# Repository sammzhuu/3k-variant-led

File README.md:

# 3k-variant-led
 a rehash of my scrapped 6k build now with 3k and leds 

if you want to build this project yourself, here are some useful guides: 
https://docs.google.com/document/d/1xsjb1sf3pxFw8bXC4gNhWsFhWNOthMoyz6RiJc1UtVI/edit?tab=t.0
https://www.youtube.com/watch?v=Ov2vdJQmaAw
https://www.masterzen.fr/2020/05/03/designing-a-keyboard-part-1/
https://wiki.ai03.com/books/pcb-design/page/pcb-guide-part-1---preparations

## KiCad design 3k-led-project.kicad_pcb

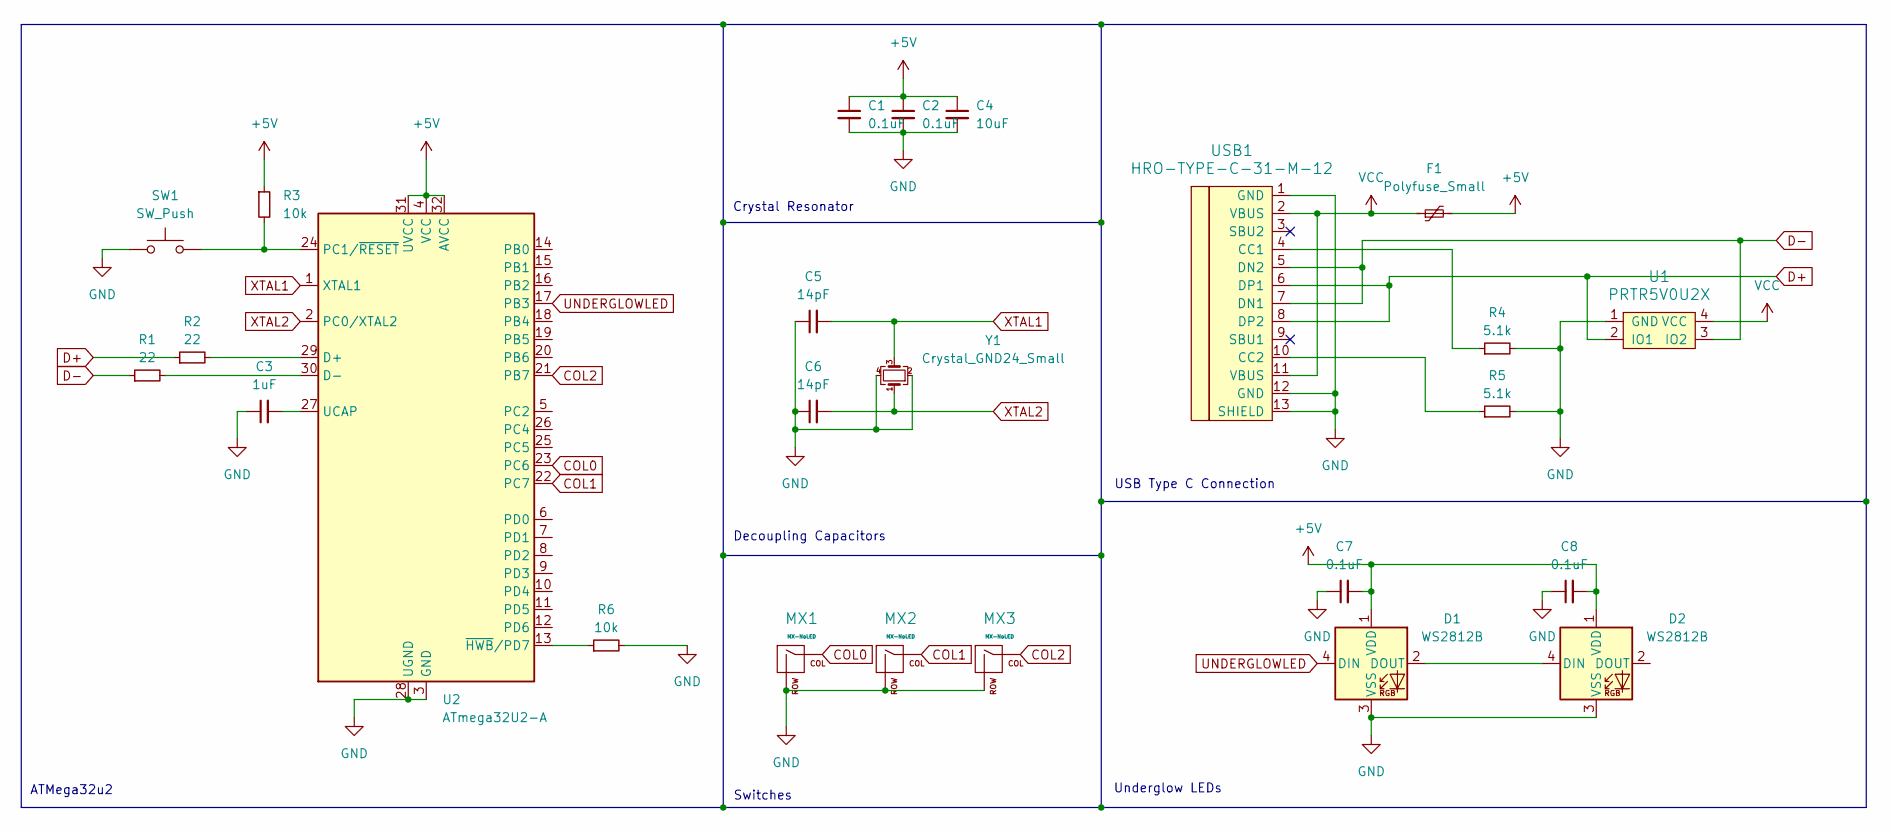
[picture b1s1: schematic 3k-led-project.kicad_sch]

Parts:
C1, C2, C7, C8: 0.1uF; C_0805_2012Metric_Pad1.18x1.45mm_HandSolder
C3: 1uF; C_0805_2012Metric_Pad1.18x1.45mm_HandSolder
C4: 10uF; C_0805_2012Metric_Pad1.18x1.45mm_HandSolder
C5, C6: 14pF; C_0805_2012Metric_Pad1.18x1.45mm_HandSolder
D1, D2: WS2812B; LED_WS2812B_PLCC4_5.0x5.0mm_P3.2mm
F1: Polyfuse_Small; Fuse_1206_3216Metric_Pad1.42x1.75mm_HandSolder
MX1, MX2, MX3: MX-NoLED; MXOnly-1U-Hotswap
R1, R2: 22; R_0805_2012Metric_Pad1.20x1.40mm_HandSolder
R3, R6: 10k; R_0805_2012Metric_Pad1.20x1.40mm_HandSolder
R4, R5: 5.1k; R_0805_2012Metric_Pad1.20x1.40mm_HandSolder
SW1: SW_Push; SKQGADE010
U1: PRTR5V0U2X; SOT143B
U2: ATmega32U2-A; TQFP-32_7x7mm_P0.8mm
USB1: HRO-TYPE-C-31-M-12; HRO-TYPE-C-31-M-12-HandSoldering
Y1: Crystal_GND24_Small; Crystal_SMD_3225-4Pin_3.2x2.5mm_HandSoldering

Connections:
+5V: C1.1, C2.1, C4.1, C7.2, C8.2, D1.1 (VDD), D2.1 (VDD), F1.2, R3.1, U2.4 (VCC), U2.31 (UVCC), U2.32 (AVCC)
COL0: MX1.1 (COL), U2.23 (PC6)
COL1: MX2.1 (COL), U2.22 (PC7)
COL2: MX3.1 (COL), U2.21 (PB7)
D+: R2.1, U1.2 (IO1), USB1.6 (DP1), USB1.8 (DP2)
D-: R1.1, U1.3 (IO2), USB1.5 (DN2), USB1.7 (DN1)
GND: C1.2, C2.2, C3.1, C4.2, C5.1, C6.1, C7.1, C8.1, D1.3 (VSS), D2.3 (VSS), MX1.2 (ROW), MX2.2 (ROW), MX3.2 (ROW), R4.2, R5.2, R6.2, SW1.1, U1.1 (GND), U2.3 (GND), U2.28 (UGND), USB1.1 (GND), USB1.12 (GND), USB1.13 (SHIELD), Y1.2, Y1.4
unnamed: D1.2 (DOUT), D2.4 (DIN)
unnamed: R2.2, U2.29 (D+)
unnamed: R1.2, U2.30 (D-)
unnamed: R3.2, SW1.2, U2.24 (PC1/~RESET)
unnamed: C3.2, U2.27 (UCAP)
unnamed: R6.1, U2.13 (~HWB/PD7)
unnamed: R4.1, USB1.4 (CC1)
unnamed: R5.1, USB1.10 (CC2)
UNDERGLOWLED: D1.4 (DIN), U2.17 (PB3)
VCC: F1.1, U1.4 (VCC), USB1.2 (VBUS), USB1.11 (VBUS)
XTAL1: C5.2, U2.1 (XTAL1), Y1.3
XTAL2: C6.2, U2.2 (PC0/XTAL2), Y1.1

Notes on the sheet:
Underglow LEDs
Crystal Resonator
Decoupling Capacitors
USB Type C Connection
Switches
ATMega32u2

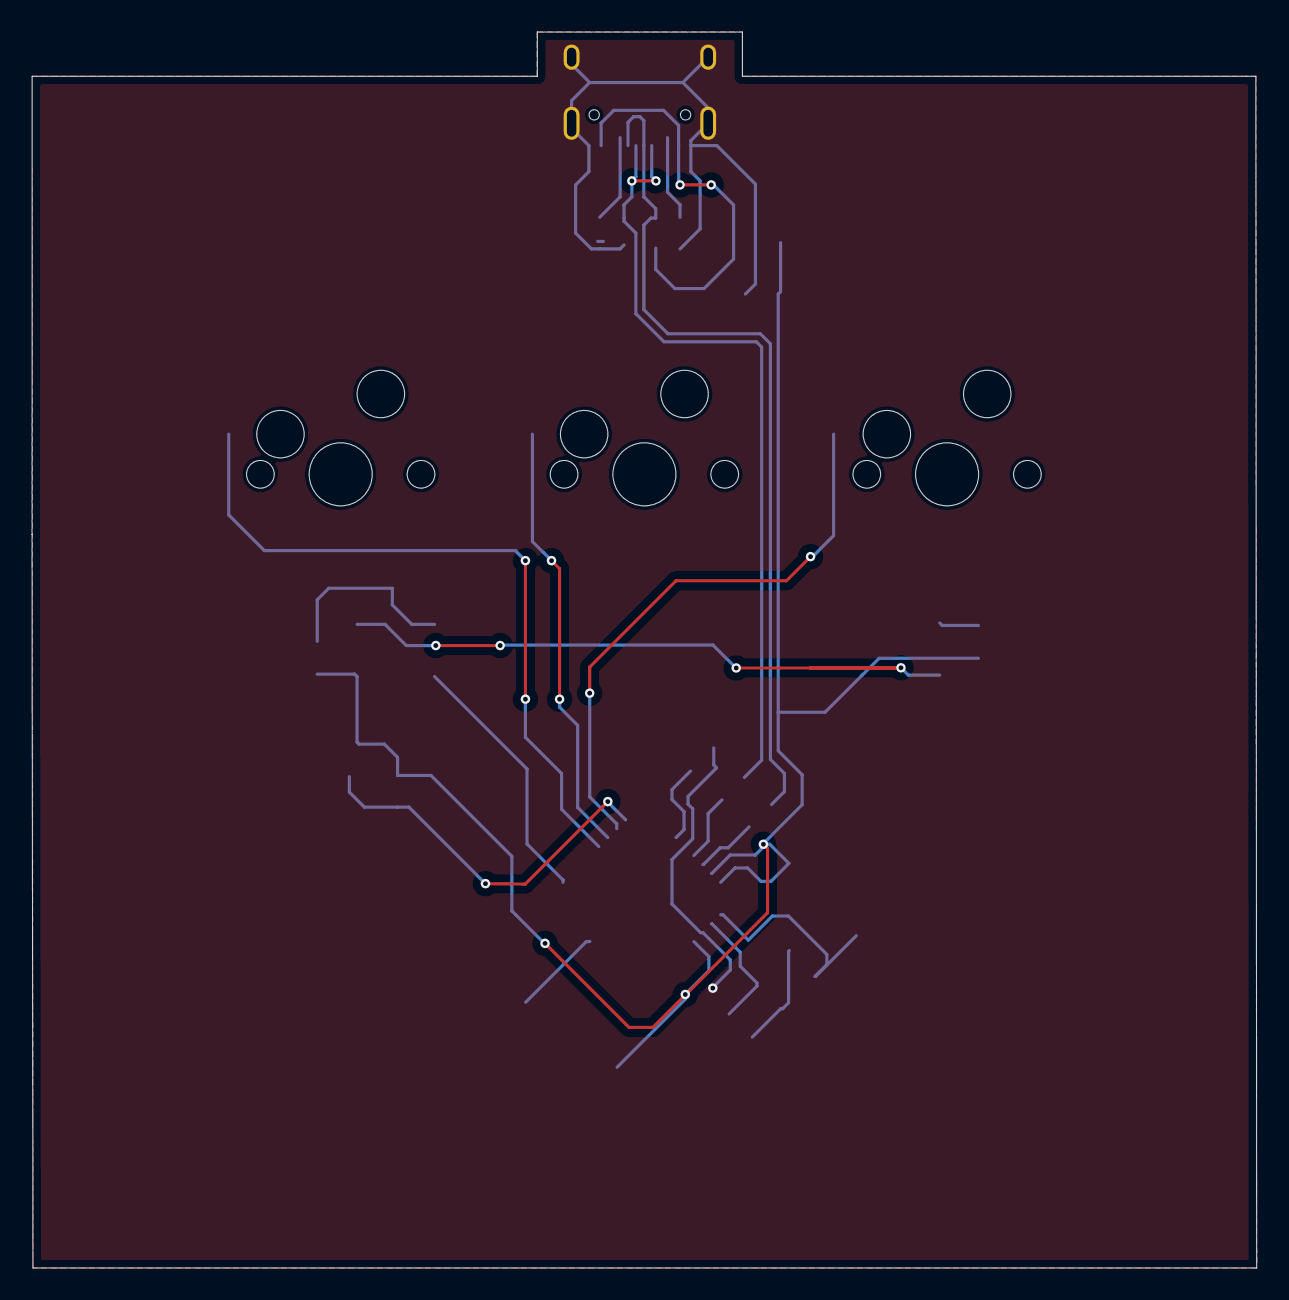
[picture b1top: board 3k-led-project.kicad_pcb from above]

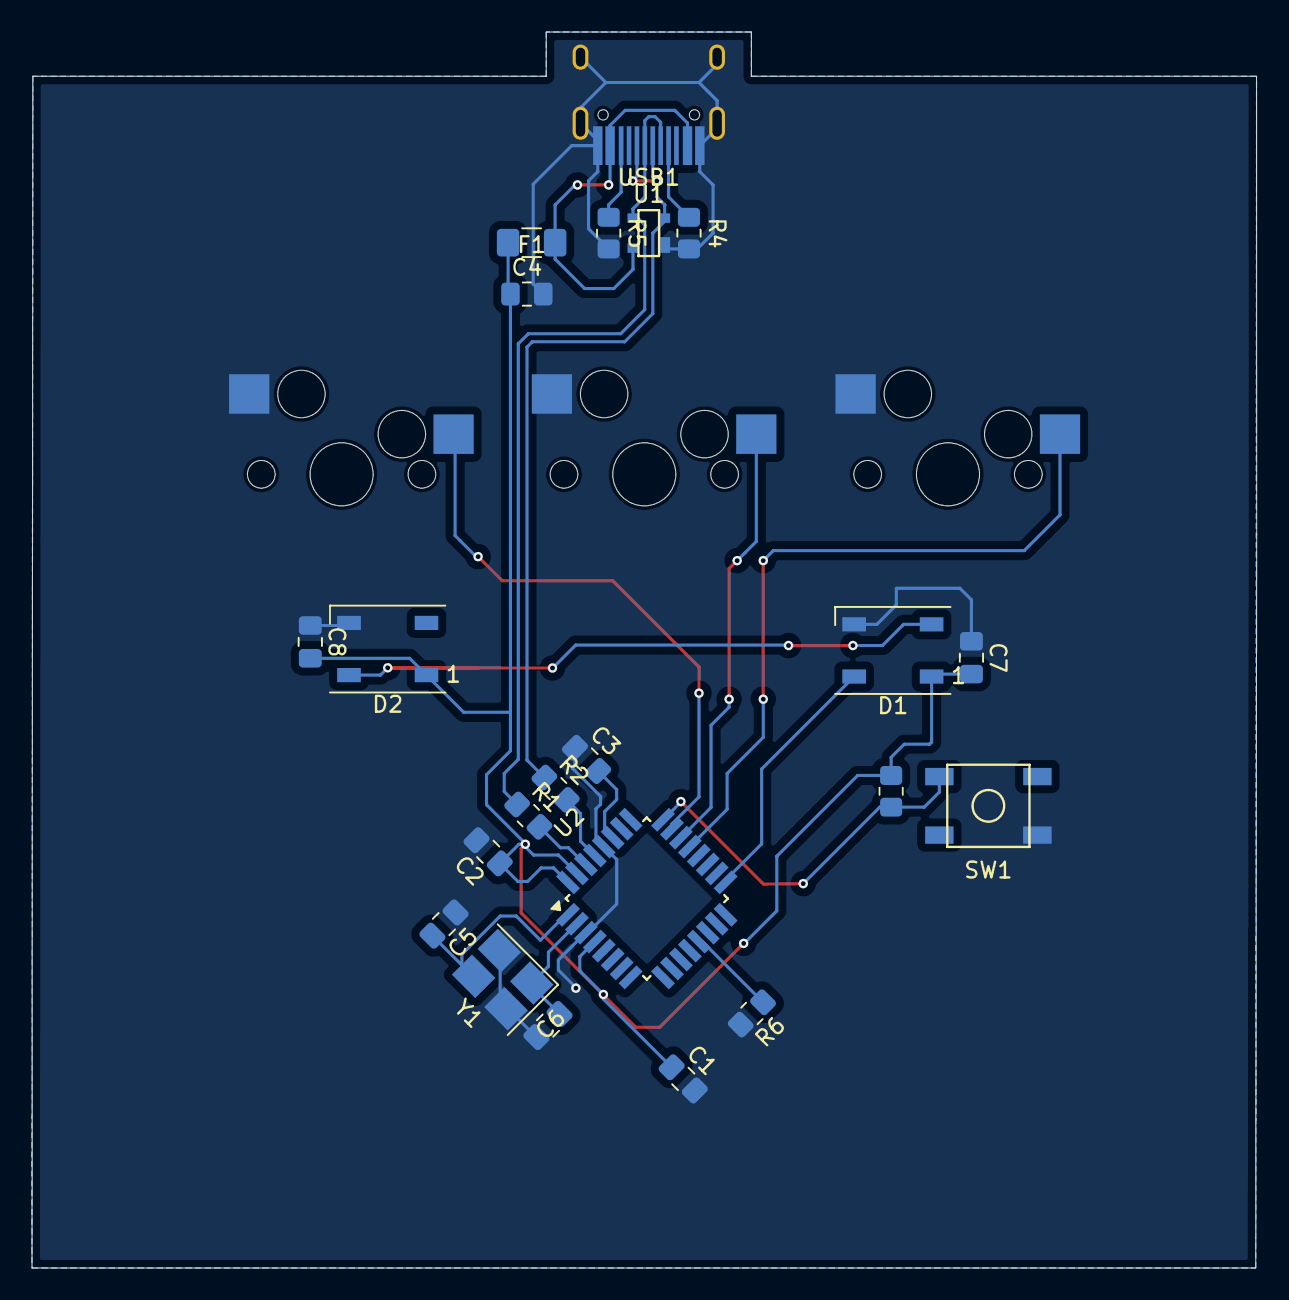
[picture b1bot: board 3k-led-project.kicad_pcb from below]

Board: 2 copper layers, 77.5 x 78.2 mm, 25 parts (22 on the bottom side), 19 nets.

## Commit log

2025-02-09 add submodules
2025-02-09 more submodules
2025-02-09 updated outdated submodule
2025-02-09 managed libraries
2025-02-09 finished schematic
2025-02-09 Create LICENSE
2025-02-09 barfed the components into the pcb and updated schematic
